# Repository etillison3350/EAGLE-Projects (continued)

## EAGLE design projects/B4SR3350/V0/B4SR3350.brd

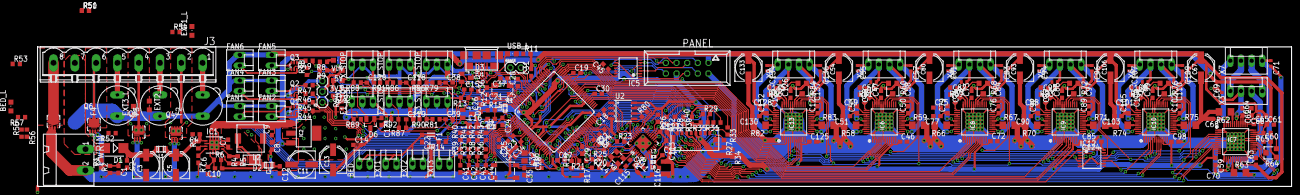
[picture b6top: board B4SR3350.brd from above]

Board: 2 copper layers, 299.1 x 33.3 mm, 309 parts (0 on the bottom side), 250 nets.

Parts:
3V3, 5V: CHIPLED_0805
BED: KK-254-2; MOLEX-KK-254-2
BED_L: CHIPLED_0805
C1, C10, C35: 10n; C0603
C2, C4, C8, C9, C12, C14, C25, C113: 10u; C0603
C3, C5, C54, C67, C80, C93, C106, C133: 100u; PANASONIC_D
C6, C15, C17, C18, C19, C20, C21, C23, C24, C27, C28, C29, C30, C31, C33, C46, C49, C50, C51, C53, C59, C62, C63, C64, C66, C72, C75, C76, C77, C79, C85, C88, C89, C90, C92, C98, C101, C102, C103, C105, C112, C124, C125, C128, C129, C130, C132: 100n; C0603
C7, C52, C65, C78, C91, C104, C131: 22n; C0603
C11: 220u; PANASONIC_D
C13: 10u; PANASONIC_D
C16, C32: 10u; C0805
C22, C41, C42, C43, C44, C45: 2.2u; C0603
C26, C47, C60, C73, C86, C99, C126: 4u7; C0603
C34: 2.2u 0.1-10ohm ESR; C0603
C36, C37: 10p; C0603
C38, C39, C118, C119, C120, C121: 2.2n; C0603
C40: 2K2; C0603
C48, C61, C74, C87, C100, C127: 470n; C0603
C55, C56, C57, C58, C68, C69, C70, C71, C81, C82, C83, C84, C94, C95, C96, C97, C107, C108, C109, C110, C134, C135, C136, C137: 470p; C0402
C111: 1u; C0603
C114, C115: 6.8p; C0603
C116: 3.0p; C0603
C117: 2.4p; C0603
D1: SMB
D2: SS1P3L; DO220AAL
D3: PRTR5V0U2XB; SOT143B
D4, D5, D6: BAT54C; SOT23
E1_STOP, E2_STOP, E3_STOP: KK-254-3; MOLEX-KK-254-3
ERASE: 1X02_SMALL
EXT1, EXT2, EXT3: KK-254-2; MOLEX-KK-254-2
EXT1_L, EXT2_L, EXT3_L: CHIPLED_0805
F1: MC36207
F2, F3, F4: 19560
FAN1, FAN2, FAN3, FAN4, FAN5, FAN6: KK-254-2; MOLEX-KK-254-2
IC1: A4403; QFN16-4X4
IC2: LDO-TS1117CW-3V3; SOT223
IC3: ATSAM4S8C; LQFP100
IC5: 74HC125TSSOP14; TSSOP14
IC6, IC7, IC8, IC9, IC10, IC13: TMC5130; QFP50P900X900X113-49N_NOFID
IC12: CD4072B-TSSOP14; TSSOP14
J1: ZX62-AB-5PA; USB-MICRO-10103594
J2: MOLEX-SD-47571-001; MOLEX-47571
J3: MSTBV8
J4: U.FL
J5: 1X03_SMALL
L1: MH2029-300Y; C0805
L2: 10uH; SRR0604
L3: MPZ2012S221A; C0805
L4, L5: 10uH 100MHz; C0603
L7: 4.3nH; C0402
L8: 2.2nH; C0402
PANEL: 057-010-1
PWRIN: MSTBA2
Q1, Q2, Q3: NX138BKS; SOT363_PHILIPS
Q4, Q5, Q6, Q7: AON7524; 3X3DFN-EP
R1, R13: 47K; R0603
R2: 4.7K; R0603
R3: 100K; R0603
R4, R5: 0R1; R0603
R6: 3K92; R0603
R7: 750R; R0603
R8, R17, R54, R55, R56, R57: 4K7; R0603
R9, R11, R22, R23, R25, R26: 2K2; R0603
R10, R50, R51, R52, R53: 180R; R0603
R12: 27K; R0603
R14, R16, R34, R35, R36, R37, R38, R39, R79, R81, R86, R87, R88, R89, R90, R91, R92, R93, R94, R95: 10K; R0603
R15: 1R; R0603
R18: 470R; R0603
R19, R20, R21: 47R; R0603
R24: 1k; R0603
R27, R28, R29, R31, R32, R33: 220R; R0603
R30: 100R; R0603
R40, R41, R42, R43: 4K7 0.1%; R0603
R44, R45, R46, R47, R48, R49: 1K; R0603
R58, R59, R62, R63, R66, R67, R70, R71, R74, R75, R82, R83: 0R11; R1206
R60, R64, R68, R72, R76, R84: 20K; RTRIM3103
R61, R65, R69, R73, R77, R85: 20K; R0603
R78: 12K 1%; R0603
R80: 200R; R0603
RESET: PTS647
U1: ESP8266; QFN32-5X5MM
U2: SOIC08-FAIRCHILD
USB_L: CHIPLED_0805
VIN: CHIPLED_0805
X1: 12MHz; 5.0X3.2_KX-9A
X2, X3, X4, X5, X6, X7, X9: KK-254-4; MOLEX-KK-254-4
X8: 3.2X2.5_KX-7
X_STOP: KK-254-3; MOLEX-KK-254-3
Y_STOP: KK-254-3; MOLEX-KK-254-3
Z_STOP: KK-254-3; MOLEX-KK-254-3

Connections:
3V3_LED: 3V3.C, R10.1
5V_E1: C126.1, IC13.33
5V_E2: C47.1, IC6.33
5V_E3: C73.1, IC8.33
5V_LED: 5V.C, R9.1
5V_X: C86.1, IC9.33
5V_Y: C99.1, IC10.33
5V_Z: C60.1, IC7.33
24V_LED: R8.1, VIN.C
+3V3: 3V3.A, C13.+, C14.1, C16.2, C17.2, C18.2, C19.2, C20.2, C21.2, C23.1, C25.1, C40.1, C45.1, C46.1, C59.1, C72.1, C85.1, C98.1, C111.1, C112.1, C113.1, C124.1, C125.1, D4.3, D5.3, D6.3, E1_STOP.2, E2_STOP.2, E3_STOP.2, ERASE.1, IC2.2, IC2.4, IC3.10, IC3.27, IC3.50, IC3.69, IC3.91, IC3.98, IC5.14, IC6.10, IC7.10, IC8.10, IC9.10, IC10.10, IC12.14, IC13.10, J2.4, L4.2, L7.1, PANEL.8, R16.2, R34.2, R35.2, R90.2, R91.2, R92.2, R93.2, R94.2, R95.2, U1.1, U1.11, U1.17, U1.29, U1.30, U2.8, X_STOP.2, Y_STOP.2, Z_STOP.2
+5V: 5V.A, C11.+, C12.1, C48.1, C61.1, C74.1, C87.1, C100.1, C127.1, IC2.3, IC6.34, IC7.34, IC8.34, IC9.34, IC10.34, IC13.34, J5.2, L3.2, PANEL.1, R61.2, R65.2, R69.2, R73.2, R77.2, R85.2
+12V: C49.2, C50.1, C51.1, C53.1, C54.+, C62.2, C63.1, C64.1, C66.1, C67.+, C75.2, C76.1, C77.1, C79.1, C80.+, C88.2, C89.1, C90.1, C92.1, C93.+, C101.2, C102.1, C103.1, C105.1, C106.+, C128.2, C129.1, C130.1, C132.1, C133.+, D1.A, F2.1, F3.1, F4.1, FAN1.1, FAN2.1, FAN3.1, FAN4.1, FAN5.1, FAN6.1, IC6.21, IC6.39, IC6.40, IC7.21, IC7.39, IC7.40, IC8.21, IC8.39, IC8.40, IC9.21, IC9.39, IC9.40, IC10.21, IC10.39, IC10.40, IC13.21, IC13.39, IC13.40, J3.7, PWRIN.1, R1.2, R54.2, R55.2, R56.2, R57.2, VIN.A
A1_E1: C134.1, IC13.46, X9.1
A1_E2: C55.1, IC6.46, X2.1
A1_E3: C81.1, IC8.46, X4.1
A1_X: C94.1, IC9.46, X5.1
A1_Y: C107.1, IC10.46, X6.1
A1_Z: C68.1, IC7.46, X7.1
A2_E1: C135.1, IC13.42, X9.2
A2_E2: C56.1, IC6.42, X2.2
A2_E3: C82.1, IC8.42, X4.2
A2_X: C95.1, IC9.42, X5.2
A2_Y: C108.1, IC10.42, X6.2
A2_Z: C69.1, IC7.42, X3.2
ADVREF: C24.1, IC3.1, L4.1, R40.2, R41.2, R42.2, R43.2
ANTENNA: C117.1, J4.SIG, L8.2
A_Z2: X3.1, X7.2
B1_E1: C136.1, IC13.15, X9.4
B1_E2: C57.1, IC6.15, X2.4
B1_E3: C83.1, IC8.15, X4.4
B1_X: C96.1, IC9.15, X5.4
B1_Y: C109.1, IC10.15, X6.4
B1_Z: C70.1, IC7.15, X3.3
B2_E1: C137.1, IC13.19, X9.3
B2_E2: C58.1, IC6.19, X2.3
B2_E3: C84.1, IC8.19, X4.3
B2_X: C97.1, IC9.19, X5.3
B2_Y: C110.1, IC10.19, X6.3
B2_Z: C71.1, IC7.19, X7.4
BED: IC3.30, R53.1
BED_D: BED_L.C, J3.8, Q7.5, Q7.6, Q7.7, Q7.8, Q7.E1, Q7.E2, Q7.PAD
BED_G: Q7.4, R53.2
BED_L: BED_L.A, R57.1
BOOT: C7.1, IC1.11
BRA_E1: IC13.44, R82.1
BRA_E2: IC6.44, R58.1
BRA_E3: IC8.44, R66.1
BRA_X: IC9.44, R70.1
BRA_Y: IC10.44, R74.1
BRA_Z: IC7.44, R62.1
BRB_E1: IC13.17, R83.1
BRB_E2: IC6.17, R59.1
BRB_E3: IC8.17, R67.1
BRB_X: IC9.17, R71.1
BRB_Y: IC10.17, R75.1
BRB_Z: IC7.17, R63.1
B_Z2: X3.4, X7.3
CLK: J2.5, R30.2
CMD: J2.3, R29.2, R35.1
CPI_E1: C131.1, IC13.37
CPI_E2: C52.1, IC6.37
CPI_E3: C78.1, IC8.37
CPI_X: C91.1, IC9.37
CPI_Y: C104.1, IC10.37
CPI_Z: C65.1, IC7.37
CPO_E1: C131.2, IC13.35
CPO_E2: C52.2, IC6.35
CPO_E3: C78.2, IC8.35
CPO_X: C91.2, IC9.35
CPO_Y: C104.2, IC10.35
CPO_Z: C65.2, IC7.35
DAT0: J2.7, R28.2
DAT1: J2.8, R32.2
DAT2: J2.1, R33.2
DAT3: J2.2, R31.2
DET: J2.G5, R27.2, R34.1
E1_DIR: IC3.75, IC13.9
E1_EN: IC3.79, IC13.3
E1_FUSED: F2.2, J3.1
E1_STEP: IC3.78, IC13.8
E1_STOP: C121.1, D6.1, IC3.8, R89.1
E1_STOP_IN: E1_STOP.1, R89.2, R94.1
E2_DIR: IC3.72, IC6.9
E2_EN: IC3.74, IC6.3
E2_FUSED: F3.2, J3.3
E2_STEP: IC3.73, IC6.8
E2_STOP: C119.1, D5.2, IC3.94, R87.1
E2_STOP_IN: E2_STOP.1, R87.2, R92.1
E3_DIR: IC3.62, IC8.9
E3_EN: IC3.66, IC8.3
E3_FUSED: F4.2, J3.5
E3_STEP: IC3.65, IC8.8
E3_STOP: C39.1, D5.1, IC3.92, R81.1
E3_STOP_IN: E3_STOP.1, R81.2, R90.1
EDR_CONN: R25.2, U1.15
ENN: IC3.71, IC6.29, IC7.29, IC8.29, IC9.29, IC10.29, IC13.29
ERASE: ERASE.2, IC3.87
ESP_CS: R26.2, U1.13
ESP_DATA_RDY: IC3.40, R25.1
ESP_EN: IC3.32, R17.1, U1.7
ESP_MISO: IC3.41, R20.2
ESP_MOSI: IC3.33, R21.2
ESP_NPCS0: IC3.42, R26.1
ESP_RESET: IC3.43, R18.1
ESP_RST: R18.2, R22.2, U1.32
ESP_SCK: IC3.31, R19.2
ESP_URXD: IC3.46, R23.1
ESP_UTXD: IC3.44, R24.1
ESP_XIN: C115.1, U1.28, X8.1
ESP_XOUT: C114.2, U1.27, X8.3
EXT1_D: EXT1_L.C, J3.2, Q4.5, Q4.6, Q4.7, Q4.8, Q4.E1, Q4.E2, Q4.PAD
EXT1_G: Q4.4, R50.2
EXT1_L: EXT1_L.A, R54.1
EXT2_D: EXT2_L.C, J3.4, Q5.5, Q5.6, Q5.7, Q5.8, Q5.E1, Q5.E2, Q5.PAD
EXT2_G: Q5.4, R51.2
EXT2_L: EXT2_L.A, R55.1
EXT3_D: EXT3_L.C, J3.6, Q6.5, Q6.6, Q6.7, Q6.8, Q6.E1, Q6.E2, Q6.PAD
EXT3_G: Q6.4, R52.2
EXT3_L: EXT3_L.A, R56.1
FAN1: IC3.21, R44.1
FAN1_D: FAN1.2, Q1.6
FAN1_G: Q2.2, R46.2
FAN1_G1: Q1.2, R44.2
FAN2: IC3.19, R45.1
FAN2_D: FAN2.2, Q1.3
FAN2_G: Q2.5, R47.2
FAN2_G1: Q1.5, R45.2
FAN3: IC3.18, R46.1
FAN3_D: FAN3.2, Q2.6
FAN3_G: Q3.2, R48.2
FAN4: IC3.76, R47.1
FAN4_D: FAN4.2, Q2.3
FAN4_G: Q3.5, R49.2
FAN5: IC3.86, R48.1
FAN5_D: FAN5.2, Q3.6
FAN6: IC3.93, R49.1
FAN6_D: FAN6.2, Q3.3
FB: C10.2, IC1.5, R6.1, R7.2
FLASH_CLK: R80.2, U2.6
FLASH_CS: U1.20, U2.1
FLASH_D: U1.23, U2.5
FLASH_HOLD: U1.18, U2.7
FLASH_Q: U1.22, U2.2
FLASH_WP: U1.19, U2.3
GND: C1.2, C2.2, C3.-, C4.2, C5.-, C6.2, C8.2, C9.2, C11.-, C12.2, C13.-, C14.2, C15.1, C16.1, C17.1, C18.1, C19.1, C20.1, C21.1, C22.2, C23.2, C24.2, C25.2, C26.2, C27.2, C28.2, C29.2, C30.2, C31.2, C32.2, C33.2, C34.2, C35.2, C36.2, C37.2, C38.2, C39.2, C40.2, C41.2, C42.2, C43.2, C44.2, C45.2, C46.2, C47.2, C48.2, C49.1, C50.2, C51.2, C54.-, C55.2, C56.2, C57.2, C58.2, C59.2, C60.2, C61.2, C62.1, C63.2, C64.2, C67.-, C68.2, C69.2, C70.2, C71.2, C72.2, C73.2, C74.2, C75.1, C76.2, C77.2, C80.-, C81.2, C82.2, C83.2, C84.2, C85.2, C86.2, C87.2, C88.1, C89.2, C90.2, C93.-, C94.2, C95.2, C96.2, C97.2, C98.2, C99.2, C100.2, C101.1, C102.2, C103.2, C106.-, C107.2, C108.2, C109.2, C110.2, C111.2, C112.2, C113.2, C114.1, C115.2, C116.2, C117.2, C118.2, C119.2, C120.2, C121.2, C124.2, C125.2, C126.2, C127.2, C128.1, C129.2, C130.2, C133.-, C134.2, C135.2, C136.2, C137.2, D3.1, E1_STOP.3, E2_STOP.3, E3_STOP.3, F1.2, IC1.2, IC1.6, IC1.7, IC1.10, IC1.13, IC1.14, IC1.15, IC1.16, IC1.EXP, IC2.1, IC3.2, IC3.26, IC3.45, IC3.61, IC3.70, IC3.77, IC3.95, IC5.1, IC5.4, IC5.7, IC5.12, IC5.13, IC6.1, IC6.2, IC6.6, IC6.13, IC6.24, IC6.31, IC6.32, IC6.36, IC6.48, IC6.PAD, IC7.1, IC7.2, IC7.6, IC7.13, IC7.24, IC7.31, IC7.32, IC7.36, IC7.48, IC7.PAD, IC8.1, IC8.2, IC8.6, IC8.13, IC8.24, IC8.31, IC8.32, IC8.36, IC8.48, IC8.PAD, IC9.1, IC9.2, IC9.6, IC9.13, IC9.24, IC9.31, IC9.32, IC9.36, IC9.48, IC9.PAD, IC10.1, IC10.2, IC10.6, IC10.13, IC10.24, IC10.31, IC10.32, IC10.36, IC10.48, IC10.PAD, IC12.7, IC12.9, IC13.1, IC13.2, IC13.6, IC13.13, IC13.24, IC13.31, IC13.32, IC13.36, IC13.48, IC13.PAD, J1.GND, J2.6, J2.G1, J2.G2, J2.G3, J4.GND1, J4.GND2, J5.3, PANEL.2, PWRIN.2, Q1.1, Q1.4, Q2.1, Q2.4, Q3.1, Q3.4, Q4.1, Q4.2, Q4.3, Q5.1, Q5.2, Q5.3, Q6.1, Q6.2, Q6.3, Q7.1, Q7.2, Q7.3, R2.1, R7.1, R8.2, R9.2, R10.2, R11.2, R13.2, R17.2, R22.1, R58.2, R59.2, R60.1, R62.2, R63.2, R64.1, R66.2, R67.2, R68.1, R70.2, R71.2, R72.1, R74.2, R75.2, R76.1, R78.1, R82.2, R83.2, R84.1, RESET.B1, RESET.B2, U1.EP, U2.4, X1.2, X1.4, X8.2, X8.4, X_STOP.3, Y_STOP.3, Z_STOP.3
HEATER1: IC3.28, R50.1
HEATER2: IC3.25, R51.1
HEATER3: IC3.24, R52.1
IDEK: C26.1, R15.1
IREF_E1: IC13.30, R84.2
IREF_E2: IC6.30, R60.2
IREF_E3: IC8.30, R68.2
IREF_X: IC9.30, R72.2
IREF_Y: IC10.30, R76.2
IREF_Z: IC7.30, R64.2
ISEN: D2.P$2, IC1.8, R4.2, R5.2
LCD_ENC_SW: IC3.82, PANEL.7
LCD_MISO: IC3.53, IC5.8
LCD_MISO_BUF: IC5.9, PANEL.6
LCD_MOSI: IC3.52, IC5.2
LCD_MOSI_BUF: IC5.3, PANEL.5
LCD_SCK: IC3.67, IC5.5
LCD_SCK_BUF: IC5.6, PANEL.4
LCD_SD_CS: IC3.80, IC5.10, PANEL.3
LNA: C116.1, L8.1, U1.2
LX: C7.2, D2.P$1, IC1.12, L2.P$1
MCCDA: IC3.59, R29.1
MCCK: IC3.63, R30.1
MCDA0: IC3.64, R28.1
MCDA1: IC3.81, R32.1
MCDA2: IC3.39, R33.1
MCDA3: IC3.57, R31.1
MISO: R20.1, U1.10
MOSI: R21.1, U1.12
MOT_MISO: IC3.15, IC6.7, IC7.7, IC8.7, IC9.7, IC10.7, IC13.7
MOT_MOSI: IC3.20, IC6.5, IC7.5, IC8.5, IC9.5, IC10.5, IC13.5
MOT_SCK: IC3.22, IC6.4, IC7.4, IC8.4, IC9.4, IC10.4, IC13.4
unnamed: IC12.2, IC12.13
PWR_FAIL_DET2: C1.1, IC3.23, R1.1, R2.2
REFIN_E1: R84.3, R85.1
REFIN_E2: R60.3, R61.1
REFIN_E3: R68.3, R69.1
REFIN_X: R72.3, R73.1
REFIN_Y: R76.3, R77.1
REFIN_Z: R64.3, R65.1
RES12K: R78.2, U1.31
RESET: C35.1, IC3.60, R16.1, RESET.A2
SAM_TFR_RDY: IC3.29, U1.16
SD_CD: IC3.58, R27.1
SERVO: IC3.13, J5.1
SGND: IC1.9, R4.1, R5.1
SG_TST: IC3.17, IC12.1
SG_TST_E1: IC12.5, IC13.27
SG_TST_E2: IC6.27, IC12.4
SG_TST_E3: IC8.27, IC12.3
SG_TST_X: IC9.27, IC12.12
SG_TST_Y: IC10.27, IC12.11
SG_TST_Z: IC7.27, IC12.10
SPCK: R19.1, U1.9
SPICLK: R80.1, U1.21
SS: C6.1, IC1.4
TON: IC1.3, R3.1
T_BED: C42.1, IC3.5, R37.1
T_BED_IN: BED.2, R37.2, R41.1
T_EXT1: C43.1, IC3.4, R38.1
T_EXT1_IN: EXT1.2, R38.2, R42.1
T_EXT2: C44.1, IC3.3, R36.1
T_EXT2_IN: EXT2.2, R36.2, R43.1
T_EXT3: C41.1, IC3.6, R39.1
T_EXT3_IN: EXT3.2, R39.2, R40.1
URXD: R23.2, U1.25
URXD1: IC3.7, PANEL.9
USB_LED: R11.1, USB_L.C
USB_N: D3.3, IC3.88, J1.D-
USB_P: D3.2, IC3.89, J1.D+
USB_PWR_MON: C15.2, IC3.68, R12.2, R13.1
UTXD: R24.2, U1.26
UTXD1: IC3.9, PANEL.10
VBUS: D3.4, J1.VBUS, R12.1, USB_L.A
VCP_E1: C132.2, IC13.38
VCP_E2: C53.2, IC6.38
VCP_E3: C79.2, IC8.38
VCP_X: C92.2, IC9.38
VCP_Y: C105.2, IC10.38
VCP_Z: C66.2, IC7.38
VDD3P3: L7.2, U1.3, U1.4
VDDOUT: C28.1, C29.1, C30.1, C31.1, C32.1, C33.1, C34.1, IC3.11, IC3.16, IC3.36, IC3.56, IC3.85, L5.2
VDDPLL: C27.1, IC3.100, L5.1, R15.2
VIN: C2.1, C3.+, D1.C, L1.1
VIN_F: C4.1, C5.+, IC1.1, L1.2, R3.2
VOUT: C8.1, C9.1, C10.1, L2.P$2, L3.1, R6.2
VSSA: BED.1, C22.1, EXT1.1, EXT2.1, EXT3.1, F1.1, R14.2
VSSA_MON: IC3.14, R14.1
XIN: C36.1, IC3.97, X1.3
XOUT: C37.1, IC3.96, X1.1
X_DIR: IC3.38, IC9.9
X_EN: IC3.55, IC9.3
X_STEP: IC3.54, IC9.8
X_STOP: C120.1, D6.2, IC3.90, R88.1
X_STOP_IN: R88.2, R93.1, X_STOP.1
Y_DIR: IC3.49, IC10.9
Y_EN: IC3.48, IC10.3
Y_STEP: IC3.47, IC10.8
Y_STOP: C118.1, D4.2, IC3.84, R86.1
Y_STOP_IN: R86.2, R91.1, Y_STOP.1
Z_DIR: IC3.34, IC7.9
Z_EN: IC3.37, IC7.3
Z_STEP: IC3.35, IC7.8
Z_STOP: C38.1, D4.1, IC3.83, R79.1
Z_STOP_IN: R79.2, R95.1, Z_STOP.1

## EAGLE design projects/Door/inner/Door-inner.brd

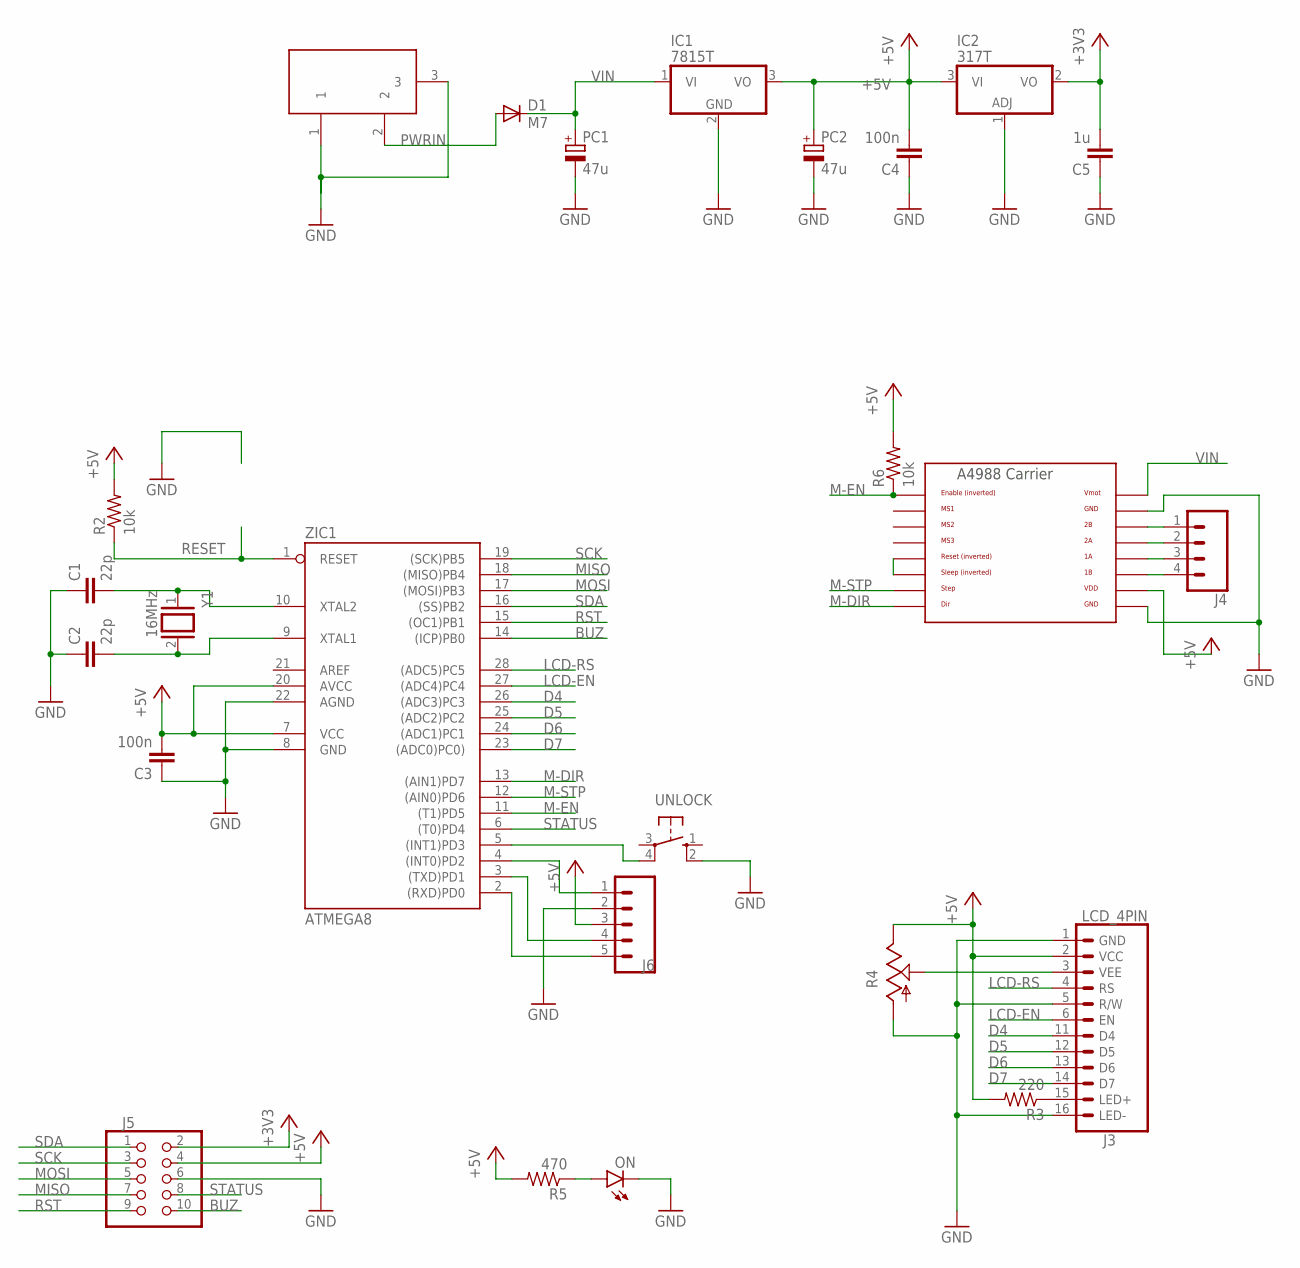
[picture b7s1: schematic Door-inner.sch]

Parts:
C1, C2: 22p; C025-030X050
C3, C4: 100n; C050-030X075
C5: 1u; C050-030X075
D1: M7; D-12.5
IC1: 7815T; TO220H
IC2: 317T; TO220H
J3: LCD_4PIN; LCD-16X2
J4: CONN_04; 1X04
J5: PINHD-2X5; 2X05
J6: CONN_05; 1X05
ON: LED3MM
PC1, PC2: 47u; TT2D5
R2, R6: 10k; 0207/10
R3: 220; 0207/10
R4: TRIM_US-S63P; S63P
R5: 470; 0207/10
U$1: A4988BREAKOUT
UNLOCK: 10-XX; B3F-10XX
X1: POWERSUPPLY_DC21MMX; POWERSUPPLY_DC-21MM
Y1: 16MHz; QS
ZIC1: ATMEGA8; DIL28-3

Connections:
+3V3: C5.2, IC2.2 (VO), J5.2
+5V: C3.2, C4.2, IC1.3 (VO), IC2.3 (VI), J3.2 (VCC), J5.4, J6.3, PC2.+, R2.2, R3.2, R4.E, R5.2, R6.2, U$1.VDD, ZIC1.7 (VCC), ZIC1.20 (AVCC)
BUZ: J5.10, ZIC1.14 ((ICP)PB0)
D4: J3.11 (D4), ZIC1.26 ((ADC3)PC3)
D5: J3.12 (D5), ZIC1.25 ((ADC2)PC2)
D6: J3.13 (D6), ZIC1.24 ((ADC1)PC1)
D7: J3.14 (D7), ZIC1.23 ((ADC0)PC0))
GND: C1.1, C2.1, C3.1, C4.1, C5.1, IC1.2 (GND), IC2.1 (ADJ), J3.1 (GND), J3.5 (R/W), J3.16 (LED-), J5.6, J6.2, ON.K (C), PC1.-, PC2.-, R4.A, U$1.GND, U$1.GND@0 (GND), UNLOCK.2 (S1), X1.1, X1.3, ZIC1.8 (GND), ZIC1.22 (AGND)
LCD-EN: J3.6 (EN), ZIC1.27 ((ADC4)PC4)
LCD-RS: J3.4 (RS), ZIC1.28 ((ADC5)PC5)
M-DIR: U$1.DIR, ZIC1.13 ((AIN1)PD7)
M-EN: R6.1, U$1.EN, ZIC1.11 ((T1)PD5)
M-STP: U$1.STEP, ZIC1.12 ((AIN0)PD6)
MISO: J5.7, ZIC1.18 ((MISO)PB4)
MOSI: J5.5, ZIC1.17 ((MOSI)PB3)
unnamed: J6.1, ZIC1.4 ((INT0)PD2)
unnamed: J6.4, ZIC1.3 ((TXD)PD1)
unnamed: J6.5, ZIC1.2 ((RXD)PD0)
unnamed: J3.15 (LED+), R3.1
unnamed: J3.3 (VEE), R4.S
unnamed: ON.A, R5.1
unnamed: U$1.RST, U$1.SLP (SLEEP)
unnamed: J4.1, U$1.2B
unnamed: J4.2, U$1.2A
unnamed: J4.3, U$1.1A
unnamed: J4.4, U$1.1B
unnamed: UNLOCK.4 (P1), ZIC1.5 ((INT1)PD3)
PWRIN: D1.A, X1.2
RESET: R2.1, ZIC1.1 (RESET)
RST: J5.9, ZIC1.15 ((OC1)PB1)
SCK: J5.3, ZIC1.19 ((SCK)PB5)
SDA: J5.1, ZIC1.16 ((SS)PB2)
STATUS: J5.8, ZIC1.6 ((T0)PD4)
VIN: D1.C, IC1.1 (VI), PC1.+, U$1.VMOT
XTAL1: C2.2, Y1.2, ZIC1.9 (XTAL1)
XTAL2: C1.2, Y1.1, ZIC1.10 (XTAL2)

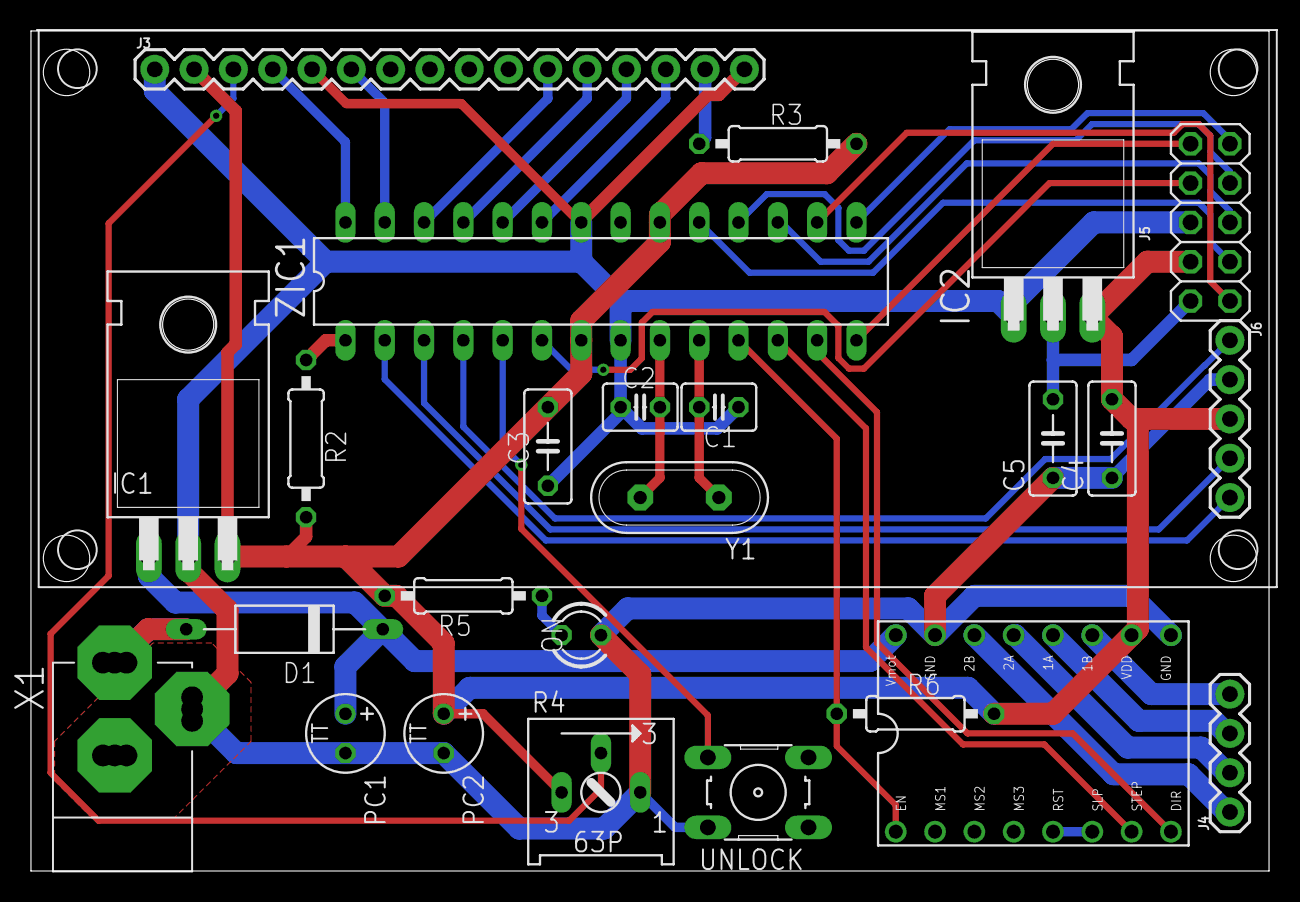
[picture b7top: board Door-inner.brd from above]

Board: 2 copper layers, 80.0 x 54.3 mm, 25 parts (0 on the bottom side), 36 nets.

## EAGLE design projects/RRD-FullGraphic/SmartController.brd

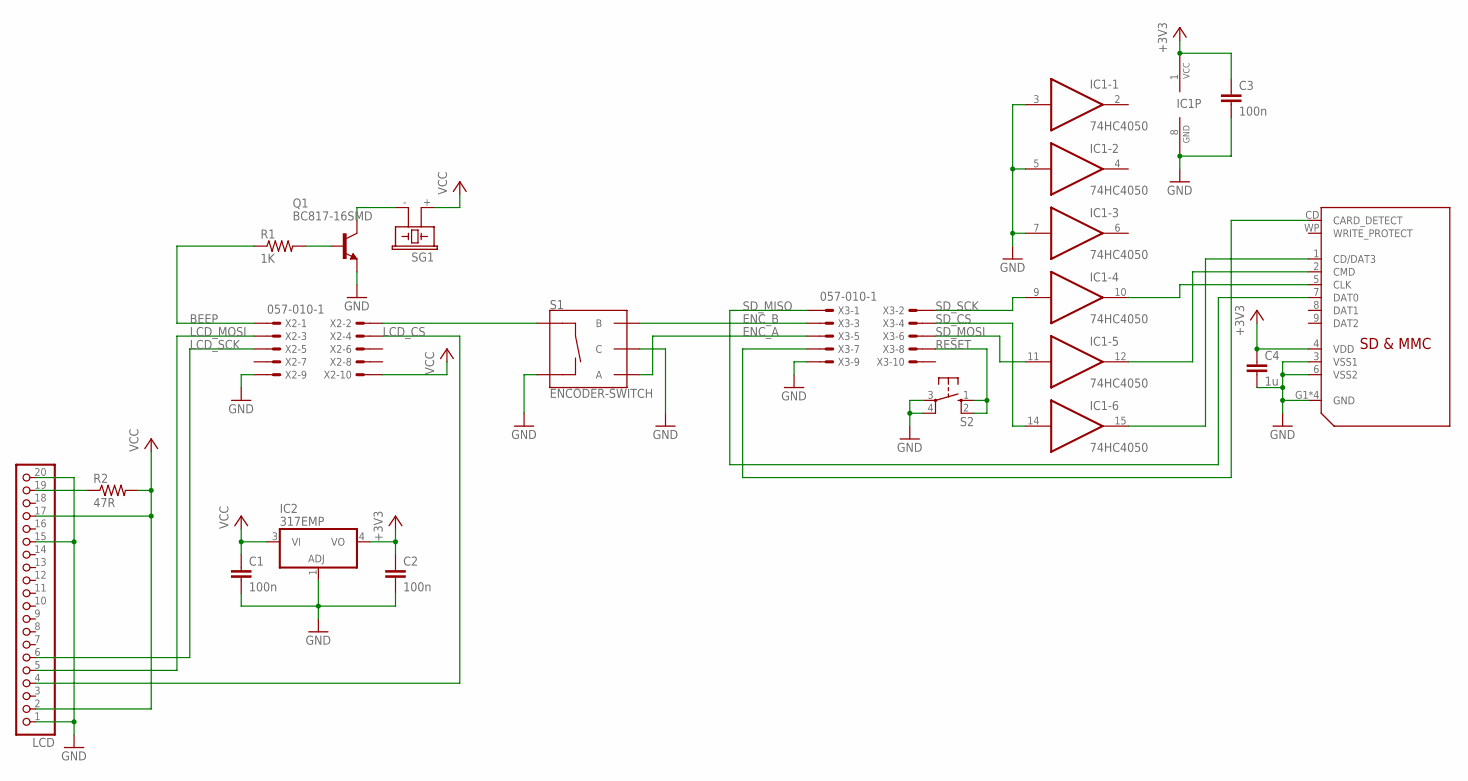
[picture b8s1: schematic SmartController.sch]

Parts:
C1, C2, C3: 100n; C0805
C4: 1u; C0805
IC1: 74HC4050; SO16
IC2: 317EMP; SOT223
LCD: PINHD-1X20; 1X20
Q1: BC817-16SMD; SOT23-BEC
R1: 1K; R0805
R2: 47R; R0805
S1: ENCODER-SWITCH; ROTARY_ENC_PLAIN
S2: 10-XX; B3F-10XX
SG1: F/CM12P
X1: TE-2041021; 2041021
X2, X3: 057-010-1

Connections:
+3V3: C2.1, C3.1, C4.1, IC1.1 (VCC), IC2.4 (VO), X1.4 (VDD)
BEEP: R1.1, X2.1
ENC_A: S1.A, X3.5
ENC_B: S1.B, X3.3
GND: C1.2, C2.2, C3.2, C4.2, IC1.3 (I), IC1.5 (I), IC1.7 (I), IC1.8 (GND), IC2.1 (ADJ), LCD.1, LCD.15, LCD.20, Q1.E, S1.C, S1.SW-, S2.3, S2.4 (P1), X1.3 (VSS1), X1.6 (VSS2), X1.G1 (GND), X1.G2 (GND), X1.G3 (GND), X1.G4 (GND), X2.9, X3.9
LCD_CS: LCD.4, X2.4
LCD_MOSI: LCD.5, X2.3
LCD_SCK: LCD.6, X2.5
unnamed: X1.CD (CARD_DETECT), X3.7
unnamed: S1.SW+, X2.2
unnamed: LCD.19, R2.1
unnamed: IC1.15 (O), X1.1 (CD/DAT3)
unnamed: IC1.12 (O), X1.2 (CMD)
unnamed: IC1.10 (O), X1.5 (CLK)
unnamed: Q1.B, R1.2
unnamed: Q1.C, SG1.- (2)
RESET: S2.1 (S), S2.2 (S1), X3.8
SD_CS: IC1.14 (I), X3.4
SD_MISO: X1.7 (DAT0), X3.1
SD_MOSI: IC1.11 (I), X3.6
SD_SCK: IC1.9 (I), X3.2
VCC: C1.1, IC2.3 (VI), LCD.2, LCD.17, R2.2, SG1.+ (1), X2.10

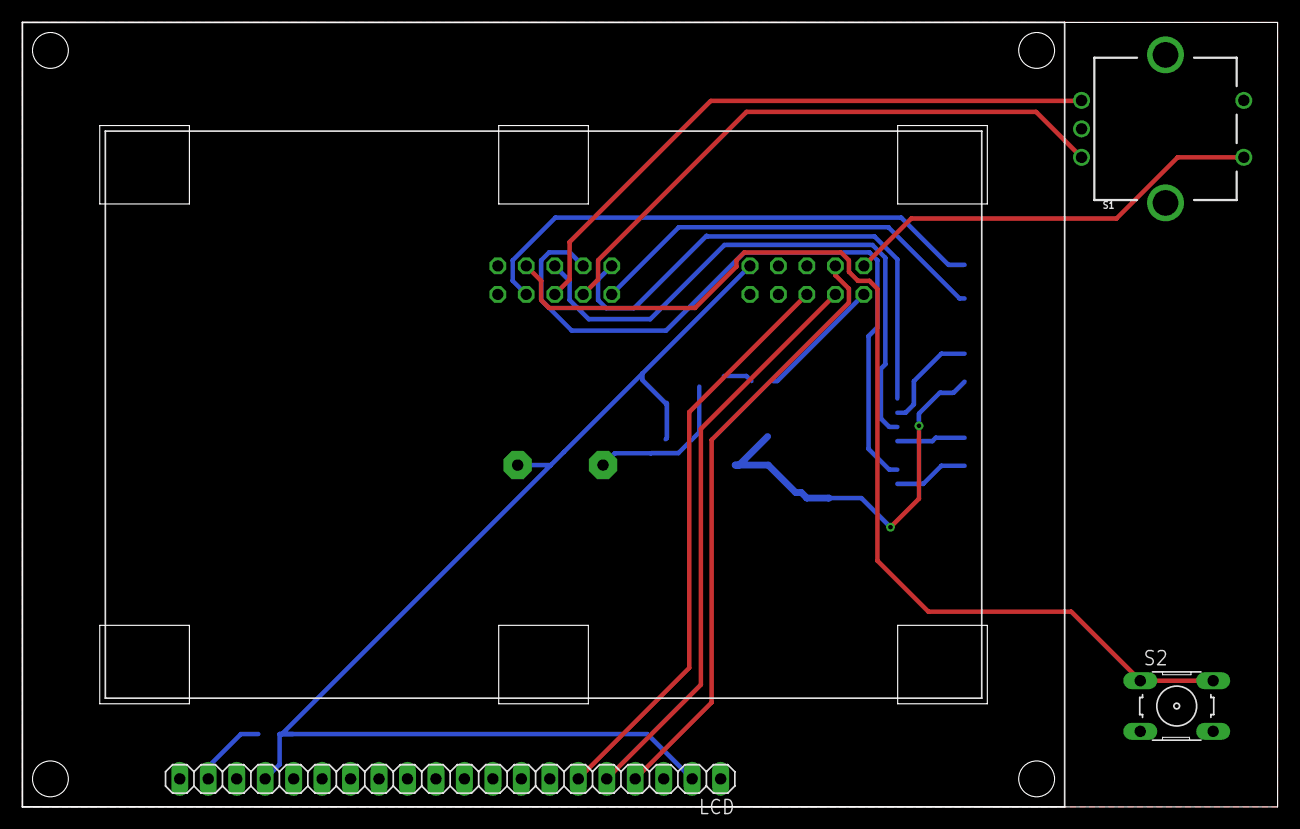
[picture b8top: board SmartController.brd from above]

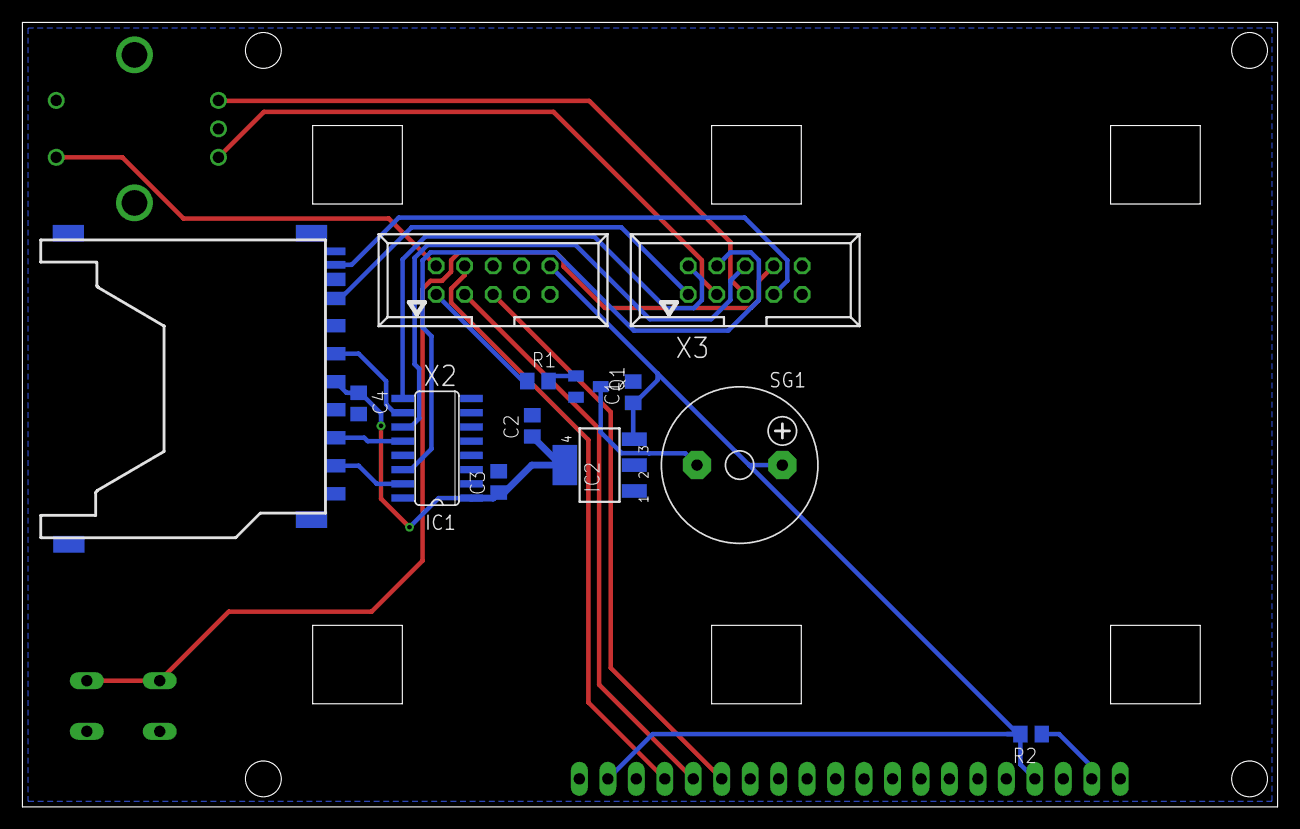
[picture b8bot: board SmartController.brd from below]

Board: 2 copper layers, 112.0 x 70.0 mm, 16 parts (13 on the bottom side), 22 nets.

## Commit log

2018-11-24 Some projects and stuff
2018-11-24 Added libraries, changed directory
2018-11-24 Didn't delete the old files (oops)
2018-11-24 Rerouted door boards for rivet-plated vias instead of plated through-holes
2018-11-24 Added Trinamic 2660 library
2018-11-26 Progress on Duet Reference
2018-11-27 Via rivets apparently have a 0.6mm INNER diameter
2018-12-14 Added voltage selection for z-stop
2018-12-21 AZR-V1
2018-12-22 58.4%
2018-12-23 More AZR development; will be changing board shape slightly
2018-12-26 AZR -> APSR v1.0.2
2018-12-31 Found all of the parts on DigiKey
    (and replaced most that didn't work, for various reasons)
2019-01-01 Changed out mosfets, other improvements (APSR)
2019-01-04 LCD screen
2019-01-07 Door-inner redesign
2019-01-09 Inner door modifications
2019-01-15 Changed something, apparently
2019-01-21 APSR Rev. 1.0.3
2019-01-23 Put all of the components on the wrong side of the board in V3
    On to V4
2019-01-24 Progress...
2019-01-24 More progress...
2019-01-25 Finished, I think
2019-01-26 Moved the labels
2019-02-14 Replacing .35mm vias with .4mm
2019-02-14 Extra vias in inner door
2019-02-14 New door, for making with plated through-holes
2019-02-15 Not exactly sure what I changed
2019-02-25 New 32-bit AMR3350 (probably will be renamed), + other edits
2019-02-26 Progress
2019-02-26 More progress
2019-03-03 Some traces
2019-03-04 Almost done*
2019-03-07 Almost** done*
2019-03-07 Done***
2019-03-07 Added a resistor
2019-03-07 Properly positioned names/labels (silkscreen)
2019-03-07 A few small changes
2019-04-04 Changes from a while back, which I think involved a different component choice?
2019-04-04 Started a new board (B4SR3350)
2019-04-21 60% of layout/routing for new B4SR
2019-05-03 Ulticontroller adapter, AZR stuff?
2019-05-04 B4SR stuff, mostly, and APSR V5 schematic
2019-09-01 AMRV7
2019-09-01 Forgot to save
2019-09-04 More more progress
2019-09-06 Almost done?
2019-09-06 20 parts left
2019-09-09 66 airwires left
2019-09-10 Done!
2019-09-12 Project change
2019-09-23 Final** version of AMRV7/EE4SR1.1.1, new APSR
2019-09-26 Progress on APSR
2019-09-26 Cleaned up the EE4SR
2019-09-27 Progress, as usual
2019-09-28 All placed and routed
2019-09-29 Done**
2019-10-04 Various small PCBs
2019-10-04 Minor improvements, cam
2019-10-14 Soldermask cut tests
2020-01-22 Mini
